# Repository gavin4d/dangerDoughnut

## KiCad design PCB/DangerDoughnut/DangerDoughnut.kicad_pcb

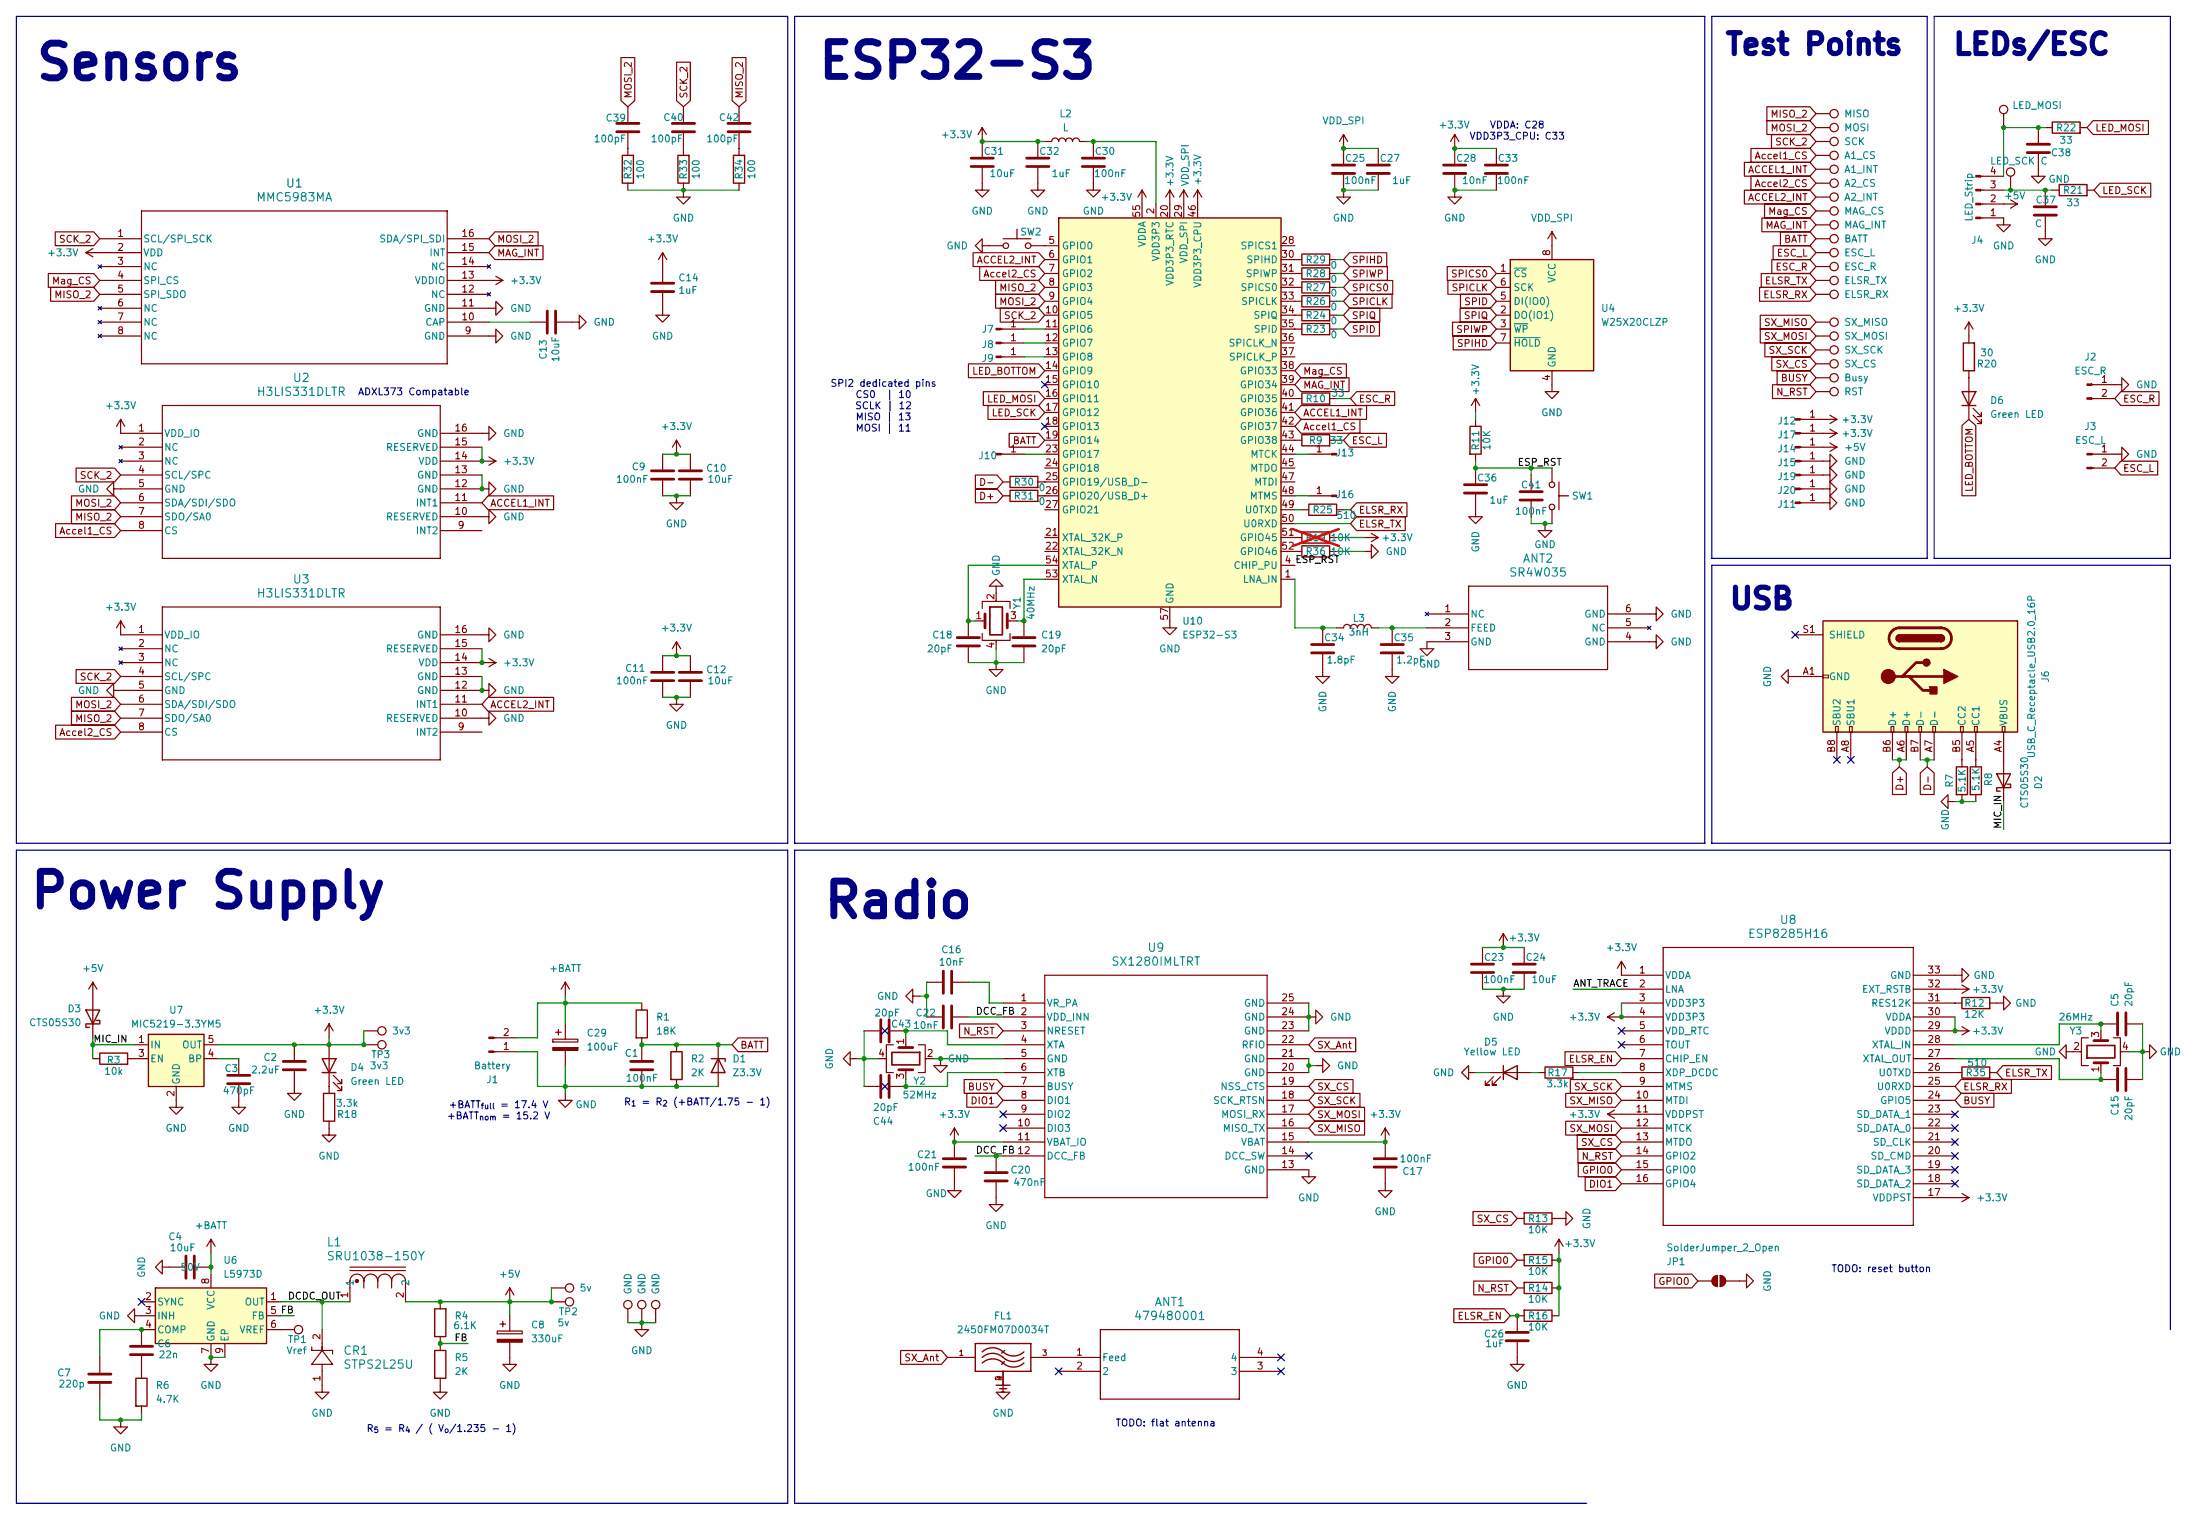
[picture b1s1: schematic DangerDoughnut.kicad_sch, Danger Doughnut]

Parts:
ANT1: 479480001; ANT_47948-0001_MOL
ANT2: SR4W035; SR4W035_4X6_ANT
C1, C9, C11, C17, C21, C23, C25, C30, C33, C41: 100nF; C_0402_1005Metric
C2: 2.2uF; C_0402_1005Metric
C3: 470pF; C_0402_1005Metric
C4: 10uF; C_1206_3216Metric_Pad1.33x1.80mm_HandSolder; Voltage 50V
C5, C15, C18, C19, C43, C44: 20pF; C_0402_1005Metric_Pad0.74x0.62mm_HandSolder
C6: 22n; C_0402_1005Metric
C7: 220p; C_0402_1005Metric
C8: 330uF; CP_Radial_D6.3mm_P2.50mm
C10, C12, C13, C24, C31: 10uF; C_0805_2012Metric_Pad1.18x1.45mm_HandSolder
C14, C26, C27, C32, C36: 1uF; C_0402_1005Metric
C16, C22, C28: 10nF; C_0402_1005Metric
C20: 470nF; C_0402_1005Metric
C29: 100uF; CP_Right_Angle_D6.3_P2.50_H16.5
C34: 1.8pF; C_0402_1005Metric
C35: 1.2pF; C_0402_1005Metric
C37, C38: C; C_0402_1005Metric
C39, C40, C42: 100pF; C_0402_1005Metric
CR1: STPS2L25U; SMB_STM
D1: Z3.3V; D_SOD-123
D2, D3: CTS05S30; D_0805_2012Metric
D4, D6: Green LED; LED_0805_2012Metric
D5: Yellow LED; LED_0805_2012Metric
FL1: 2450FM07D0034T; FIL_2450FM07D0034T; PARTREV 1.2
J1: Battery; AMASS_XT30PW-M_1x02_P2.50mm_Horizontal
J2: ESC_R; JST_S02B-PASK-2_LF__SN__1
J3: ESC_L; JST_S02B-PASK-2_LF__SN__1
J4: LED_Strip; JST_S04B-PASK-2_LF__SN_
J6: USB_C_Receptacle_USB2.0_16P; USB_C_Receptacle_GCT_USB4105-xx-A_16P_TopMnt_Horizontal
J7, J8, J9, J10, J11, J12, J13, J14, J15, J16, J17, J19, J20: Conn_01x01_Pin; SolderWirePad_1x01_SMD_1x2mm
JP1: SolderJumper_2_Open; SolderJumper-2_P1.3mm_Open_RoundedPad1.0x1.5mm
L1: SRU1038-150Y; DR74
L2: L; L_0402_1005Metric_Pad0.77x0.64mm_HandSolder
L3: 3nH; L_0402_1005Metric_Pad0.77x0.64mm_HandSolder
R1: 18K; R_0402_1005Metric
R2, R5: 2K; R_0402_1005Metric
R3: 10k; R_0402_1005Metric
R4: 6.1K; R_0402_1005Metric
R6: 4.7K; R_0402_1005Metric
R7, R8: 5.1K; R_0402_1005Metric
R9, R10, R21, R22: 33; R_0402_1005Metric
R11, R13, R14, R15, R16, R36: 10K; R_0402_1005Metric
R12: 12K; R_0402_1005Metric
R17, R18: 3.3k; R_0402_1005Metric
R19: 10K; R_0402_1005Metric; not fitted
R20: 30; R_0402_1005Metric
R23, R24, R26, R27, R28, R29, R30, R31: 0; R_0402_1005Metric
R25, R35: 510; R_0402_1005Metric
R32, R33, R34: 100; R_0402_1005Metric
SW1, SW2: SW_Push; Pad_Button
TP1: Vref; TestPoint_Pad_D1.0mm
TP2: 5v; TestPoint_Pad_D1.0mm
TP3: 3v3; TestPoint_Pad_D1.0mm
TP4: SX_MISO; Test_Via_small
TP5: MISO; Test_Via
TP6: MOSI; Test_Via
TP7: SCK; Test_Via
TP8: ELSR_TX; Test_Via
TP9: ELSR_RX; Test_Via
TP10: A1_CS; Test_Via
TP11: A1_INT; Test_Via
TP12: A2_CS; Test_Via
TP13: A2_INT; Test_Via
TP14: MAG_CS; Test_Via
TP15: MAG_INT; Test_Via
TP16: BATT; Test_Via
TP17: SX_MOSI; Test_Via_small
TP18: LED_MOSI; Test_Via
TP19: LED_SCK; Test_Via
TP20: ESC_L; Test_Via
TP21: ESC_R; Test_Via
TP22: SX_SCK; Test_Via_small
TP23: SX_CS; Test_Via_small
TP24: Busy; Test_Via_small
TP25: RST; Test_Via_small
TP26: 5v; Test_Via
TP27: 3v3; Test_Via
TP28, TP29, TP30: GND; Test_Via
U1: MMC5983MA; MMC5983MA_MEM
U2, U3: H3LIS331DLTR; QFN_31DLTR_STM
U4: W25X20CLZP; SOIC-8_5.23x5.23mm_P1.27mm
U6: L5973D; HSOP-8-1EP_3.9x4.9mm_P1.27mm_EP2.41x3.1mm_ThermalVias
U7: MIC5219-3.3YM5; SOT-23-5
U8: ESP8285H16; QFN32_5X5_EXP
U9: SX1280IMLTRT; QFN24_4X4_SEM
U10: ESP32-S3; QFN-56-1EP_7x7mm_P0.4mm_EP4x4mm
Y1: 40MHz; Crystal_SMD_2016-4Pin_2.0x1.6mm
Y2: 52MHz; Crystal_SMD_2016-4Pin_2.0x1.6mm
Y3: 26MHz; Crystal_SMD_2016-4Pin_2.0x1.6mm

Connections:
+3.3V: C2.1, C9.1, C10.2, C11.1, C12.2, C14.2, C17.2, C21.1, C23.1, C24.1, C28.1, C31.1, C32.1, C33.1, D4.2 (A), J12.1, J17.1, L2.1, R11.1, R14.1, R15.1, R16.1, R19.2, R20.2, TP3.1, TP27.1, U1.2 (VDD), U1.13 (VDDIO), U2.1 (VDD_IO), U2.14 (VDD), U2.15 (RESERVED), U3.1 (VDD_IO), U3.14 (VDD), U3.15 (RESERVED), U7.5 (OUT), U8.1 (VDDA), U8.3 (VDD3P3), U8.4 (VDD3P3), U8.11 (VDDPST), U8.17 (VDDPST), U8.29 (VDDD), U8.30 (VDDA), U8.32 (EXT_RSTB), U9.11 (VBAT_IO), U9.15 (VBAT), U10.20 (VDD3P3_RTC), U10.46 (VDD3P3_CPU), U10.55 (VDDA), U10.56 (VDDA)
+5V: C8.1, D3.2 (A), J4.2, J14.1, L1.2, R4.2, TP2.1, TP26.1
+BATT: C4.2, C29.1, J1.2, R1.1, U6.8 (VCC)
/ANT_TRACE: U8.2 (LNA)
/DCC_FB: C20.1, C22.1, U9.2 (VDD_INN), U9.12 (DCC_FB)
/DCDC_OUT: CR1.2, L1.1, U6.1 (OUT)
/ESP_RST: C36.1, C41.1, R11.2, SW1.1, U10.4 (CHIP_PU)
/FB: R4.1, R5.1, U6.5 (FB)
/MIC_IN: D2.1 (K), D3.1 (K), R3.1, U7.1 (IN)
ACCEL1_INT: TP11.1, U2.11 (INT1), U10.41 (GPIO36)
ACCEL2_INT: TP13.1, U3.11 (INT1), U10.6 (GPIO1)
Accel1_CS: TP10.1, U2.8 (CS), U10.42 (GPIO37)
Accel2_CS: TP12.1, U3.8 (CS), U10.7 (GPIO2)
BATT: C1.1, D1.1 (K), R1.2, R2.1, TP16.1, U10.19 (GPIO14)
BUSY: TP24.1, U8.24 (GPIO5), U9.7 (BUSY)
D+: J6.A6 (D+), J6.B6 (D+), R31.1
D-: J6.A7 (D-), J6.B7 (D-), R30.1
DIO1: U8.16 (GPIO4), U9.8 (DIO1)
ELSR_EN: C26.1, R16.2, U8.7 (CHIP_EN)
ELSR_RX: R25.2, TP9.1, U8.25 (U0RXD)
ELSR_TX: R35.2, TP8.1, U10.50 (U0RXD)
ESC_L: J3.2, R9.2, TP20.1
ESC_R: J2.2, R10.2, TP21.1
GND: ANT2.3 (GND), ANT2.4 (GND), ANT2.6 (GND), C1.2, C2.2, C3.2, C4.1, C5.2, C7.1, C8.2, C9.2, C10.1, C11.2, C12.1, C13.2, C14.1, C15.2, C16.2, C17.1, C18.2, C19.2, C20.2, C21.2, C22.2, C23.2, C24.2, C25.2, C26.2, C27.2, C28.2, C29.2, C30.2, C31.2, C32.2, C33.2, C34.2, C35.2, C36.2, C37.2, C38.2, C41.2, C43.1, C44.1, CR1.1, D1.2 (A), D5.1 (K), FL1.2, FL1.4, J1.1, J2.1, J3.1, J4.1, J6.A1 (GND), J6.A12 (GND), J6.B1 (GND), J6.B12 (GND), J11.1, J15.1, J19.1, J20.1, JP1.1 (A), R2.2, R5.2, R6.2, R7.2, R8.2, R12.2, R13.1, R18.1, R32.1, R33.1, R34.1, R36.2, SW1.2, SW2.1, TP28.1, TP29.1, TP30.1, U1.9 (GND), U1.11 (GND), U2.5 (GND), U2.10 (RESERVED), U2.12 (GND), U2.13 (GND), U2.16 (GND), U3.5 (GND), U3.10 (RESERVED), U3.12 (GND), U3.13 (GND), U3.16 (GND), U4.4 (GND), U6.3 (INH), U6.7 (GND), U6.9 (EP), U7.2 (GND), U8.33 (GND), U9.5 (GND), U9.13 (GND), U9.20 (GND), U9.21 (GND), U9.23 (GND), U9.24 (GND), U9.25 (GND), U10.57 (GND), Y1.2, Y1.4, Y2.2, Y2.4, Y3.2, Y3.4
GPIO0: JP1.2 (B), R15.2, U8.15 (GPIO0)
LED_BOTTOM: D6.1 (K), U10.14 (GPIO9)
LED_MOSI: R22.2, U10.16 (GPIO11)
LED_SCK: R21.2, U10.17 (GPIO12)
MAG_INT: TP15.1, U1.15 (INT), U10.39 (GPIO34)
MISO_2: C42.1, TP5.1, U1.5 (SPI_SDO), U2.7 (SDO/SA0), U3.7 (SDO/SA0), U10.8 (GPIO3)
MOSI_2: C39.1, TP6.1, U1.16 (SDA/SPI_SDI), U2.6 (SDA/SDI/SDO), U3.6 (SDA/SDI/SDO), U10.9 (GPIO4)
Mag_CS: TP14.1, U1.4 (SPI_CS), U10.38 (GPIO33)
N_RST: R14.2, TP25.1, U8.14 (GPIO2), U9.3 (NRESET)
unnamed: ANT1.1 (Feed), FL1.3
unnamed: ANT2.2 (FEED), C35.1, L3.2
unnamed: C6.1, R6.1
unnamed: C30.1, L2.2, U10.2 (VDD3P3), U10.3 (VDD3P3)
unnamed: C39.2, R32.2
unnamed: C40.2, R33.2
unnamed: C42.2, R34.2
unnamed: D2.2 (A), J6.A4 (VBUS), J6.A9 (VBUS), J6.B4 (VBUS), J6.B9 (VBUS)
unnamed: D4.1 (K), R18.2
unnamed: D5.2 (A), R17.1
unnamed: D6.2 (A), R20.1
unnamed: C37.1, J4.3, R21.1, TP19.1
unnamed: C38.1, J4.4, R22.1, TP18.1
unnamed: J6.A5 (CC1), R8.1
unnamed: J6.B5 (CC2), R7.1
unnamed: J7.1, U10.11 (GPIO6)
unnamed: J8.1, U10.12 (GPIO7)
unnamed: J9.1, U10.13 (GPIO8)
unnamed: J10.1, U10.23 (GPIO17)
unnamed: J13.1, U10.44 (MTCK)
unnamed: J16.1, U10.48 (MTMS)
unnamed: C13.1, U1.10 (CAP)
unnamed: C6.2, C7.2, U6.4 (COMP)
unnamed: TP1.1, U6.6 (VREF)
unnamed: C3.1, U7.4 (BP)
unnamed: R3.2, U7.3 (EN)
unnamed: R12.1, U8.31 (RES12K)
unnamed: R35.1, U8.26 (U0TXD)
unnamed: R17.2, U8.8 (XDP_DCDC)
unnamed: C5.1, U8.28 (XTAL_IN), Y3.3
unnamed: C15.1, U8.27 (XTAL_OUT), Y3.1
unnamed: C16.1, U9.1 (VR_PA)
unnamed: C43.2, U9.4 (XTA), Y2.1
unnamed: C44.2, U9.6 (XTB), Y2.3
unnamed: SW2.2, U10.5 (GPIO0)
unnamed: R30.2, U10.25 (GPIO19/USB_D-)
unnamed: R31.2, U10.26 (GPIO20/USB_D+)
unnamed: R10.1, U10.40 (GPIO35)
unnamed: R9.1, U10.43 (GPIO38)
unnamed: R19.1, U10.51 (GPIO45)
unnamed: R36.1, U10.52 (GPIO46)
unnamed: C34.1, L3.1, U10.1 (LNA_IN)
unnamed: R26.1, U10.33 (SPICLK)
unnamed: R27.1, U10.32 (SPICS0)
unnamed: R23.1, U10.35 (SPID)
unnamed: R29.1, U10.30 (SPIHD)
unnamed: R24.1, U10.34 (SPIQ)
unnamed: R28.1, U10.31 (SPIWP)
unnamed: R25.1, U10.49 (U0TXD)
unnamed: C19.1, U10.53 (XTAL_N), Y1.3
unnamed: C18.1, U10.54 (XTAL_P), Y1.1
SCK_2: C40.1, TP7.1, U1.1 (SCL/SPI_SCK), U2.4 (SCL/SPC), U3.4 (SCL/SPC), U10.10 (GPIO5)
SPICLK: R26.2, U4.6 (SCK)
SPICS0: R27.2, U4.1 (~CS)
SPID: R23.2, U4.5 (DI(IO0))
SPIHD: R29.2, U4.7 (~HOLD)
SPIQ: R24.2, U4.2 (DO(IO1))
SPIWP: R28.2, U4.3 (~WP)
SX_Ant: FL1.1, U9.22 (RFIO)
SX_CS: R13.2, TP23.1, U8.13 (MTDO), U9.19 (NSS_CTS)
SX_MISO: TP4.1, U8.10 (MTDI), U9.16 (MISO_TX)
SX_MOSI: TP17.1, U8.12 (MTCK), U9.17 (MOSI_RX)
SX_SCK: TP22.1, U8.9 (MTMS), U9.18 (SCK_RTSN)
VDD_SPI: C25.1, C27.1, U4.8 (VCC), U10.29 (VDD_SPI)

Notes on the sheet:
Sensors
TODO: reset button
USB
ESP32-S3
Radio
Test Points
ADXL373 Compatable
+BATT_{full} = 17.4 V +BATT_{nom} = 15.2 V
LEDs/ESC
Power Supply
TODO: flat antenna
SPI2 dedicated pins CS0 | 10 SCLK | 12 MISO | 13 MOSI | 11
R_{5} = R_{4} / ( V_{o}/1.235 - 1)
VDDA: C28 VDD3P3_CPU: C33
R_{1} = R_{2} (+BATT/1.75 - 1)

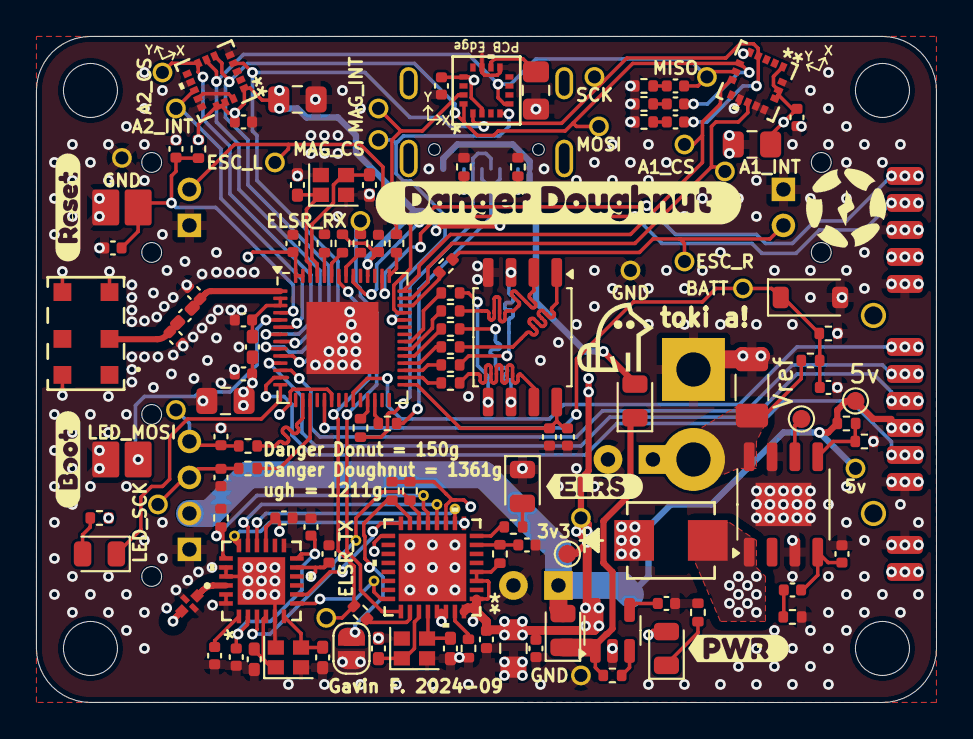
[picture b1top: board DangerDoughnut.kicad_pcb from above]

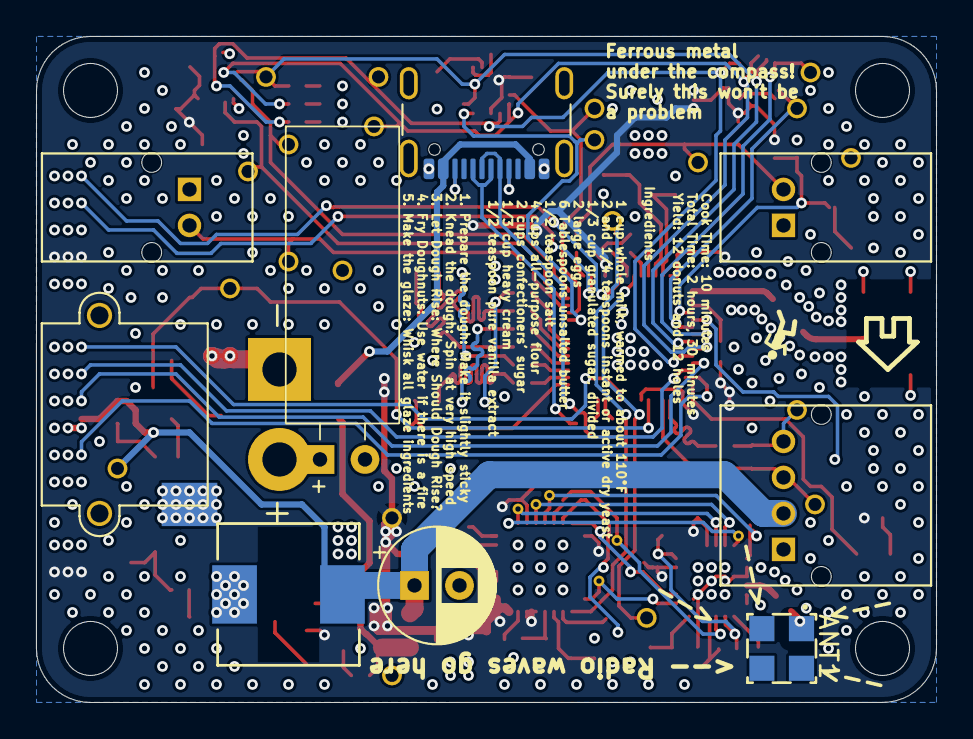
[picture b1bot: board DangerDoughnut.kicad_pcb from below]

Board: 4 copper layers, 50.0 x 37.0 mm, 161 parts (9 on the bottom side), 96 nets.

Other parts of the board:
kibuzzard-66EFAD11: G***; kibuzzard-66EFAD11
kibuzzard-66EFAD22: G***; kibuzzard-66EFAD22
kibuzzard-66F236AA: G***; kibuzzard-66F236AA
kibuzzard-672AA985: G***; kibuzzard-672AA985
kibuzzard-66936F84: G***; kibuzzard-66936F84

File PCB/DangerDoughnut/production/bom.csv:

Designator,Footprint,Quantity,Value,LCSC Part #
"_120, _119, _118, _117, _116, _115, _114, _113, _112, _111, _110, _109, _108, _107, _106, _105, _104, _103, _102, _101, _100, _99, _98, _97, _96, _95, _94, _93, _92, _91, _90, _89, _88, _87, _86, _85, _84, _83, _82, _81, _80, _79, _78, _77, _76, _75, _74, _73, _72, _71, _70, _69, _68, _67, _66, _65, _64, _63, _62, _61, _60, _59, _58, _57, _56, _55, _54, _53, _52, _51, _50, _49, _48, _47, _46, _45, _44, _43, _42, _41, _40, _39, _38, _37, _36, _35, _34, _33, _32, _31, _30, _29, _28, _27, _26, _25, _24, _23, _22, _21, _20, _19, _18, _17, _16, _15, _14, _13, _12, _11, _10, _9, _8, _7, _6, _5, _4, _3, _2, ",,120,,
ANT1,ANT_47948-0001_MOL,1,479480001,
ANT2,SR4W035_4X6_ANT,1,SR4W035,
"C1, C11, C17, C21, C23, C25, C30, C33, C41, C9",0402,10,100nF,
"C10, C12, C13, C24, C31",0805,5,10uF,
"C14, C26, C27, C32, C36",0402,5,1uF,
"C15, C18, C19, C43, C44, C5",0402,6,20pF,
"C16, C22, C28",0402,3,10nF,
C2,0402,1,2.2uF,
C20,0402,1,470nF,
C29,CP_Right_Angle_D6.3_P2.50_H16.5,1,100uF,
C3,0402,1,470pF,
C34,0402,1,1.8pF,
C35,0402,1,1.2pF,
"C37, C38",0402,2,C,
"C39, C40, C42",0402,3,100pF,
C4,1206,1,10uF,
C6,0402,1,22n,
C7,0402,1,220p,
C8,CP_Radial_D6.3mm_P2.50mm,1,330uF,
CR1,SMB_STM,1,STPS2L25U,
D1,D_SOD-123,1,Z3.3V,
"D2, D3",0805,2,CTS05S30,
"D4, D6",0805,2,Green LED,
D5,0805,1,Yellow LED,
FL1,FIL_2450FM07D0034T,1,2450FM07D0034T,
J1,AMASS_XT30PW-M_1x02_P2.50mm_Horizontal,1,Battery,
"J10, J11, J12, J13, J14, J15, J16, J17, J19, J20, J7, J8, J9",SolderWirePad_1x01_SMD_1x2mm,13,Conn_01x01_Pin,
J2,JST_S02B-PASK-2_LF__SN__1,1,ESC_R,
J3,JST_S02B-PASK-2_LF__SN__1,1,ESC_L,
J4,JST_S04B-PASK-2_LF__SN_,1,LED_Strip,
J6,USB_C_Receptacle_GCT_USB4105-xx-A_16P_TopMnt_Horizontal,1,USB_C_Receptacle_USB2.0_16P,
L1,DR74,1,SRU1038-150Y,
L2,0402,1,L,
L3,0402,1,3nH,
R1,0402,1,18K,
"R10, R21, R22, R9",0402,4,33,
"R11, R13, R14, R15, R16, R19, R3, R36",0402,8,10K,
R12,0402,1,12K,
"R17, R18",0402,2,3.3k,
"R2, R5",0402,2,2K,
R20,0402,1,30,
"R23, R24, R26, R27, R28, R29, R30, R31",0402,8,0,
"R25, R35",0402,2,510,
"R32, R33, R34",0402,3,100,
R4,0402,1,6.1K,
R6,0402,1,4.7K,
"R7, R8",0402,2,5.1K,
"SW1, SW2",Pad_Button,2,SW_Push,
TP1,TestPoint_Pad_D1.0mm,1,Vref,
TP10,Test_Via,1,A1_CS,
TP11,Test_Via,1,A1_INT,
TP12,Test_Via,1,A2_CS,
TP13,Test_Via,1,A2_INT,
TP14,Test_Via,1,MAG_CS,
TP15,Test_Via,1,MAG_INT,
TP16,Test_Via,1,BATT,
TP17,Test_Via_small,1,SX_MOSI,
TP18,Test_Via,1,LED_MOSI,
TP19,Test_Via,1,LED_SCK,
TP2,TestPoint_Pad_D1.0mm,1,5v,
TP20,Test_Via,1,ESC_L,
TP21,Test_Via,1,ESC_R,
TP22,Test_Via_small,1,SX_SCK,
TP23,Test_Via_small,1,SX_CS,
TP24,Test_Via_small,1,Busy,
TP25,Test_Via_small,1,RST,
TP26,Test_Via,1,5v,
TP27,Test_Via,1,3v3,
"TP28, TP29, TP30",Test_Via,3,GND,
TP3,TestPoint_Pad_D1.0mm,1,3v3,
TP4,Test_Via_small,1,SX_MISO,
TP5,Test_Via,1,MISO,
TP6,Test_Via,1,MOSI,
TP7,Test_Via,1,SCK,
TP8,Test_Via,1,ELSR_TX,
TP9,Test_Via,1,ELSR_RX,
U1,MMC5983MA_MEM,1,MMC5983MA,
U10,QFN-56-1EP_7x7mm_P0.4mm_EP4x4mm,1,ESP32-S3,
"U2, U3",QFN_31DLTR_STM,2,H3LIS331DLTR,
U4,SOIC-8_5.23x5.23mm_P1.27mm,1,W25X20CLZP,
U6,HSOP-8-1EP_3.9x4.9mm_P1.27mm_EP2.41x3.1mm_ThermalVias,1,L5973D,
U7,SOT-23-5,1,MIC5219-3.3YM5,
U8,QFN32_5X5_EXP,1,ESP8285H16,
U9,QFN24_4X4_SEM,1,SX1280IMLTRT,
Y1,Crystal_SMD_2016-4Pin_2.0x1.6mm,1,40MHz,
Y2,Crystal_SMD_2016-4Pin_2.0x1.6mm,1,52MHz,
Y3,Crystal_SMD_2016-4Pin_2.0x1.6mm,1,26MHz,

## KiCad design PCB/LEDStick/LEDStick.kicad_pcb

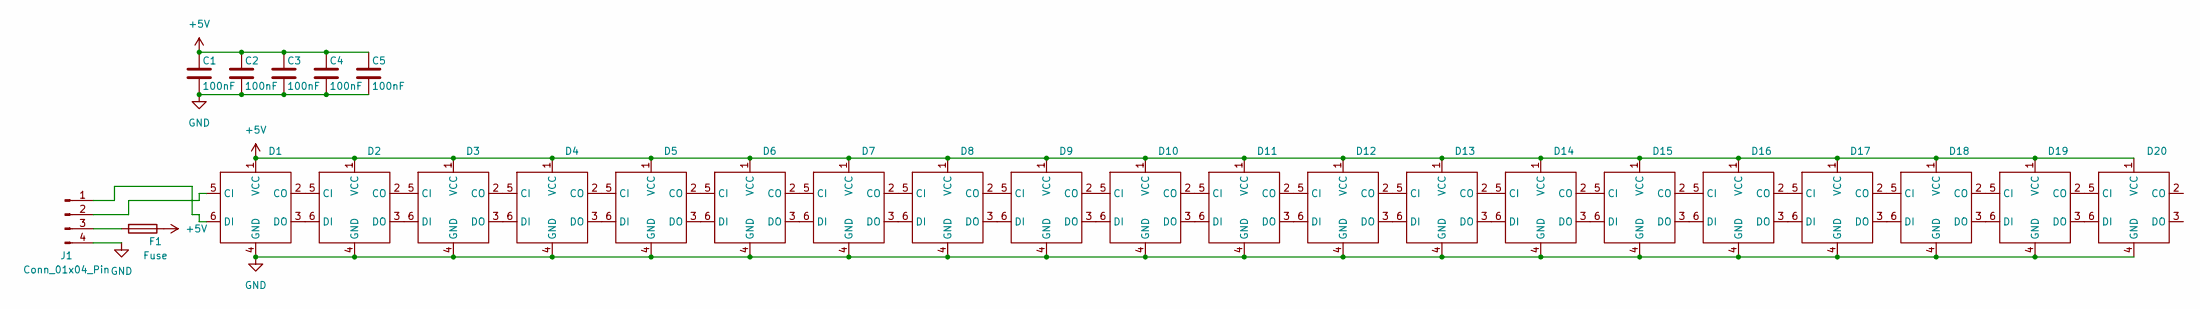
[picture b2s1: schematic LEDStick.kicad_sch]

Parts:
C1, C2, C3, C4, C5: 100nF; C_0603_1608Metric
D1, D2, D3, D4, D5, D6, D7, D8, D9, D10, D11, D12, D13, D14, D15, D16, D17, D18, D19, D20: HD107s
F1: Fuse; Fuse_0603_1608Metric
J1: Conn_01x04_Pin; JST_S04B-PASK-2_LF__SN_

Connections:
+5V: C1.1, C2.1, C3.1, C4.1, C5.1, D1.1 (VCC), D2.1 (VCC), D3.1 (VCC), D4.1 (VCC), D5.1 (VCC), D6.1 (VCC), D7.1 (VCC), D8.1 (VCC), D9.1 (VCC), D10.1 (VCC), D11.1 (VCC), D12.1 (VCC), D13.1 (VCC), D14.1 (VCC), D15.1 (VCC), D16.1 (VCC), D17.1 (VCC), D18.1 (VCC), D19.1 (VCC), D20.1 (VCC), F1.1
GND: C1.2, C2.2, C3.2, C4.2, C5.2, D1.4 (GND), D2.4 (GND), D3.4 (GND), D4.4 (GND), D5.4 (GND), D6.4 (GND), D7.4 (GND), D8.4 (GND), D9.4 (GND), D10.4 (GND), D11.4 (GND), D12.4 (GND), D13.4 (GND), D14.4 (GND), D15.4 (GND), D16.4 (GND), D17.4 (GND), D18.4 (GND), D19.4 (GND), D20.4 (GND), J1.4
unnamed: D1.5 (CI), J1.2
unnamed: D1.2 (CO), D2.5 (CI)
unnamed: D1.6 (DI), J1.1
unnamed: D1.3 (DO), D2.6 (DI)
unnamed: D2.2 (CO), D3.5 (CI)
unnamed: D2.3 (DO), D3.6 (DI)
unnamed: D3.2 (CO), D4.5 (CI)
unnamed: D3.3 (DO), D4.6 (DI)
unnamed: D4.2 (CO), D5.5 (CI)
unnamed: D4.3 (DO), D5.6 (DI)
unnamed: D5.2 (CO), D6.5 (CI)
unnamed: D5.3 (DO), D6.6 (DI)
unnamed: D6.2 (CO), D7.5 (CI)
unnamed: D6.3 (DO), D7.6 (DI)
unnamed: D7.2 (CO), D8.5 (CI)
unnamed: D7.3 (DO), D8.6 (DI)
unnamed: D8.2 (CO), D9.5 (CI)
unnamed: D8.3 (DO), D9.6 (DI)
unnamed: D9.2 (CO), D10.5 (CI)
unnamed: D10.2 (CO), D11.5 (CI)
unnamed: D9.3 (DO), D10.6 (DI)
unnamed: D10.3 (DO), D11.6 (DI)
unnamed: D11.2 (CO), D12.5 (CI)
unnamed: D11.3 (DO), D12.6 (DI)
unnamed: D12.2 (CO), D13.5 (CI)
unnamed: D12.3 (DO), D13.6 (DI)
unnamed: D13.2 (CO), D14.5 (CI)
unnamed: D13.3 (DO), D14.6 (DI)
unnamed: D14.2 (CO), D15.5 (CI)
unnamed: D14.3 (DO), D15.6 (DI)
unnamed: D15.2 (CO), D16.5 (CI)
unnamed: D15.3 (DO), D16.6 (DI)
unnamed: D16.2 (CO), D17.5 (CI)
unnamed: D16.3 (DO), D17.6 (DI)
unnamed: D17.2 (CO), D18.5 (CI)
unnamed: D17.3 (DO), D18.6 (DI)
unnamed: D18.2 (CO), D19.5 (CI)
unnamed: D18.3 (DO), D19.6 (DI)
unnamed: D19.2 (CO), D20.5 (CI)
unnamed: D19.3 (DO), D20.6 (DI)
unnamed: F1.2, J1.3

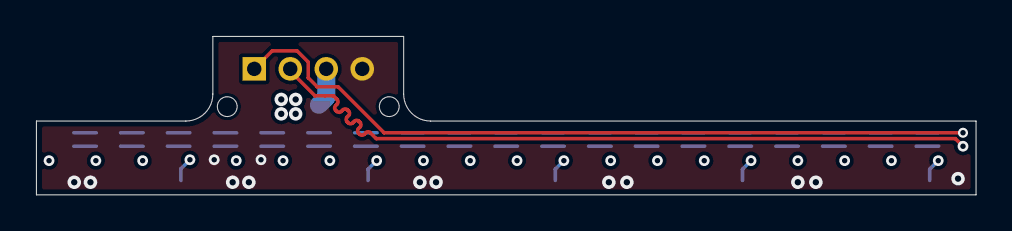
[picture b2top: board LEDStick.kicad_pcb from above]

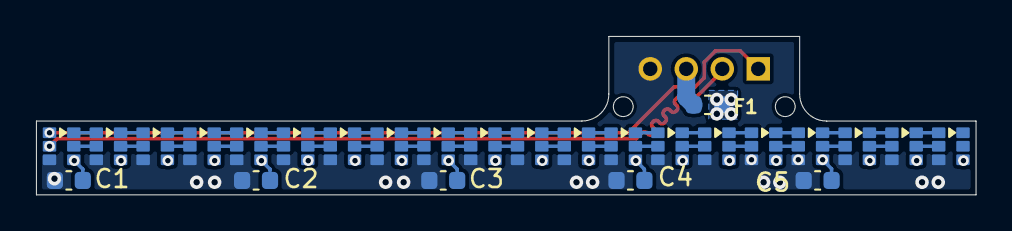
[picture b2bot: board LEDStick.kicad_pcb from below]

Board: 4 copper layers, 52.2 x 8.8 mm, 27 parts (26 on the bottom side), 43 nets.

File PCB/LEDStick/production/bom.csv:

Designator,Footprint,Quantity,Value,LCSC Part #
"C1, C2, C3, C4, C5",0603,5,100nF,
"D1, D10, D11, D12, D13, D14, D15, D16, D17, D18, D19, D2, D20, D3, D4, D5, D6, D7, D8, D9",HD107s,20,~,
F1,0603,1,Fuse,
J1,JST_S04B-PASK-2_LF__SN_,1,Conn_01x04_Pin,

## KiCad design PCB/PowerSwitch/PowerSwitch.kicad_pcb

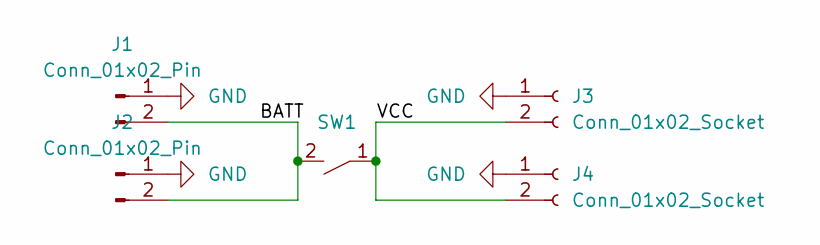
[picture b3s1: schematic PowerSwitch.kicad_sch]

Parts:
J1, J2: Conn_01x02_Pin; AMASS_XT30UPB-F_1x02_P5.0mm_Vertical
J3, J4: Conn_01x02_Socket; AMASS_XT30UPB-F_1x02_P5.0mm_Vertical
SW1: SMTSO2515_Switch

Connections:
/BATT: J1.2, J2.2, SW1.2
/VCC: J3.2, J4.2, SW1.1
GND: J1.1, J2.1, J3.1, J4.1

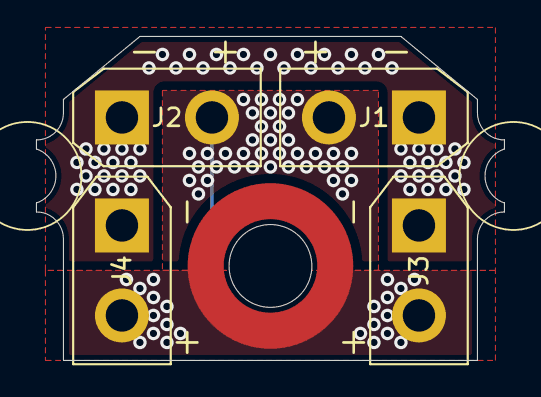
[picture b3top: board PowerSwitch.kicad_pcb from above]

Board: 4 copper layers, 26.0 x 18.0 mm, 5 parts (0 on the bottom side), 3 nets.

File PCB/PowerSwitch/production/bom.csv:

Designator,Footprint,Quantity,Value,LCSC Part #
"J1, J2",AMASS_XT30UPB-F_1x02_P5.0mm_Vertical,2,Conn_01x02_Pin,
"J3, J4",AMASS_XT30UPB-F_1x02_P5.0mm_Vertical,2,Conn_01x02_Socket,
SW1,SMTSO2515_Switch,1,~,

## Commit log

2024-08-08 angled xt30
2024-08-08 right angle xt30
2024-09-10 verified elsr
2024-09-13 updated schematic
2024-09-21 updated schematic power layout done
2024-09-22 updated layout
2024-09-24 updated layout needs 3v3 headers testpoints and verify
2024-09-24 Added silkscreen
2024-09-26 main layout complete needs headers and testpoints
2024-09-29 esp32 pins checked
2024-10-19 test points done
2024-10-20 Layout Done
2024-10-24 boards ordered
2025-03-31 added a few things
2025-03-31 gitignore
2025-03-31 readme
2025-03-31 telo impl
2025-06-06 We are spinning!
2025-06-06 Sensors and feedforwards physics
2025-06-06 removed gcode
2025-06-08 refactored a lot of orientator
2025-06-08 added connection detection
2025-11-01 updated git ignore
2025-11-01 added esp-dev
2026-05-02 NHRL1
